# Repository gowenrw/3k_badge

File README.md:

# 3k_badge

3000 Society Badge Documents

## File Structure

This is the file structure of this repository

* 3k_badge_eda - Electronic Design Automation files for the badge PCB (EDA is KiCad)
  * 3000_Society_Badge_K5 - KiCad 5.x project folder for the 3000 Society Conference version of the badge
  * DC27_3000_Society_Badge_K5 - KiCad 5.x project folder for the Defcon 27 Conference version of the badge
* code - Code for programming the badge
  * 3kcode - Current python code for trinket m0 controlling the bage
* docs - Documentation created by this project related to the badge
* graphics - Artwork and other graphics created by this project for the badge
  * fonts - Truetype fonts used in the Illustrator files
* reference - Documentation pulled from other sources related to the badge components

## Badge Details

Details on the badge can be found on the website https://3kbadge.altbier.us/

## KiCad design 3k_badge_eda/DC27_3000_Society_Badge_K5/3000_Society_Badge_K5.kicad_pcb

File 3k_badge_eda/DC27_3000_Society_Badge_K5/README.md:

# 3000_Society_Badge_K5

This directory contains the KiCad version 5.x project files for the 3000 Society Badge.

Here is the layout of the project directory:
* ./ - The root directory contains the main KiCad files for the project
  * <filename>.pro: project file. Holds parameters that apply to the entire project (schematic and PCB layout).
  * <filename>.sch: schematic file.
  * <filename>.kicad_pcb: the new PCB layout file.
  * <filename>.net: netlist in "Pcbnew" format
  * <filename>.bak: backup of schematic file.
  * <filename>.kicad_pcb-bak: backup of the new PCB layout file.
  * <filename>-cache.lib: a local cache copy of all the symbols used in the schematic
  * fp-lib-table: Footprint library list
  * sym-lib-table: Schematic library list
* ./lib_sh - This directory contains schematic library files
  * <filename>.lib: schematic symbols library file.
* ./lib_fp - This directory contains footprint module directories
  * <dirname>.pretty: footprint module directory
    * <filename>.mod: footprint module file
* ./3d_models - This directory contains footprint 3d model files
  * <filename>.wrl: VRML 3D model used in the 3D viewer to represent parts.
* ./gerber - This directory contains gerber formatted files for manufacturing

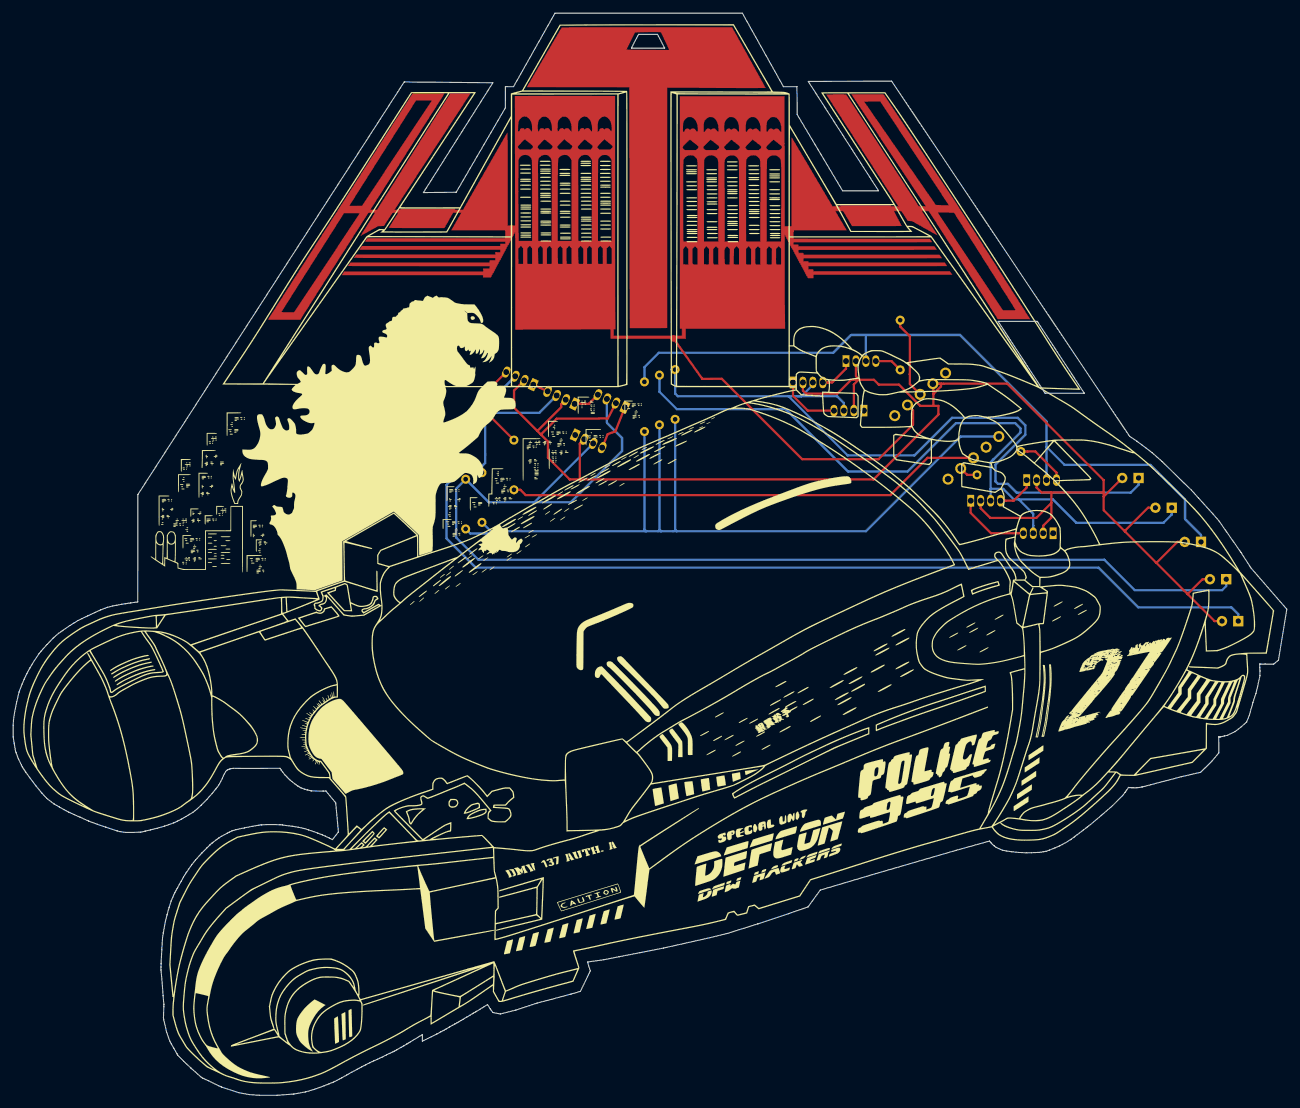
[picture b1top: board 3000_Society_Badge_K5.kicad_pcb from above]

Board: 2 copper layers, 195.2 x 165.8 mm, 25 parts (0 on the bottom side), 21 nets.

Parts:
C1, C2, C3, C4, C5: 100uF; CP_Radial_D6.3mm_P2.50mm
D10, D11, D12, D13, D21, D22, D41, D42: LED_NeoPixel_THT_5mm; LED_D5.0mm-4_RGB_Neo
D20, D40: LED_NeoPixel_THT_8mm; LED_D8.0mm-4_RGB_Neo
IC1: Trinket_M0
R1, R2, R4, R5, R10, R20, R40: 470 ohm; R_Axial_DIN0207_L6.3mm_D2.5mm_P7.62mm_Horizontal
R3: 100 ohm; R_Axial_DIN0207_L6.3mm_D2.5mm_P7.62mm_Horizontal
TP1: TouchPad; Tyrell_Touch_Pad

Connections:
unnamed: C1.1, D10.3, D11.3, R1.2
unnamed: C1.2, C2.2, C3.2, C4.2, C5.2, D10.2, D11.2, D12.2, D13.2, D20.2, D21.2, D22.2, D40.2, D41.2, D42.2, IC1.2
unnamed: C2.1, D12.3, D13.3, R2.2
unnamed: C3.1, D20.3, D40.3, R3.2
unnamed: C4.1, D21.3, D22.3, R4.2
unnamed: C5.1, D41.3, D42.3, R5.2
unnamed: D10.1, D11.4
unnamed: D10.4, R10.2
unnamed: D11.1, D12.4
unnamed: D12.1, D13.4
unnamed: D20.1, D21.4
unnamed: D20.4, R20.2
unnamed: D21.1, D22.4
unnamed: D40.1, D41.4
unnamed: D40.4, R40.2
unnamed: D41.1, D42.4
unnamed: IC1.3, R40.1
unnamed: IC1.4, TP1.1
unnamed: IC1.7, R20.1
unnamed: IC1.8, R10.1
unnamed: IC1.10, R1.1, R2.1, R3.1, R4.1, R5.1

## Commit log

2019-03-05 push_of_file_structure
2019-03-05 initial_push_of_reference_and_code
2019-03-06 Lots of updates to code
2019-03-07 KiCad_base_files
2019-03-07 new_shape_graphic
2019-03-09 graphic-work
2019-03-11 started_kicad_work
2019-03-12 kicad-library-updates-for-trinket
2019-03-12 kicad-library-updates
2019-03-13 more-artwork
2019-03-16 graphics-update
2019-03-20 some test code and a new part to test
2019-03-21 code changes to test neopixels
2019-03-22 more neopixel testing
2019-03-23 code updates for neopixels
2019-03-23 Kicad Library Updates
2019-03-23 Started EDA project over using KiCad 5.1
2019-03-24 KiCad part schematic and footprint definitions
2019-03-24 Graphic export and KiCad import tasks
2019-03-25 Candy is dandy but liquor is quicker!
2019-03-25 Schematic-Updates
2019-03-26 code updates for additional neopixels and touch
2019-03-26 PCB-updates
2019-03-27 parts customization
2019-03-27 updates to footprints
2019-03-28 3d model updates
2019-03-28 Footprint and model cleanup
2019-03-29 removing footprint cache and adding it to gitignore
2019-03-30 pcb work
2019-03-30 Graphic file cleanup removing files no longer relevent
2019-03-30 Added Copper Touch Pad to PCB
2019-03-31 Documentation Updates
2019-03-31 Back Silkscreen Work
2019-03-31 Set theme jekyll-theme-time-machine
2019-03-31 Create CNAME
2019-03-31 Document updates
2019-03-31 Board Layout Updates
2019-03-31 Generated gerber files for prototype run.
2019-04-01 added_trinket_reference
2019-04-09 started corrections from prototype
2019-04-09 corrections from 1st prototype run
2019-04-10 minor-code-chages
2019-04-16 Touch panel sensitivity adjustment
2019-04-19 white-logo-for-lanyards
2019-04-19 added a new led mode and cleaned up code
2019-04-26 Document updates and corrections
2019-05-06 Updates to component listing.
2019-06-19 started-defcon-version
2019-07-07 DC27_badge_redesign
2019-07-17 website content update
2019-07-17 website updates
2019-07-18 More documentation updates
2019-07-19 Assembly details and pics
2019-07-19 Correction to assembly instructions
2019-07-19 Formatting of assembly page
2019-07-19 I hate how github converts markdown to html!
2019-07-19 Maybe Ill eventually make the assembly page look good
2019-07-19 Does it even obey html tags?
2019-07-19 Ug assembly again
2019-07-19 assembly page old school
2019-07-19 Added I want one page and some other doc cleanup.
2019-07-19 I want one formatting fix
2019-07-19 i want one page formatting
2019-07-19 i want one updates
2019-07-19 more document updates
2019-07-19 typo
2019-07-19 Lots of document updates
2019-07-19 code document update
2019-07-23 New badge photo
